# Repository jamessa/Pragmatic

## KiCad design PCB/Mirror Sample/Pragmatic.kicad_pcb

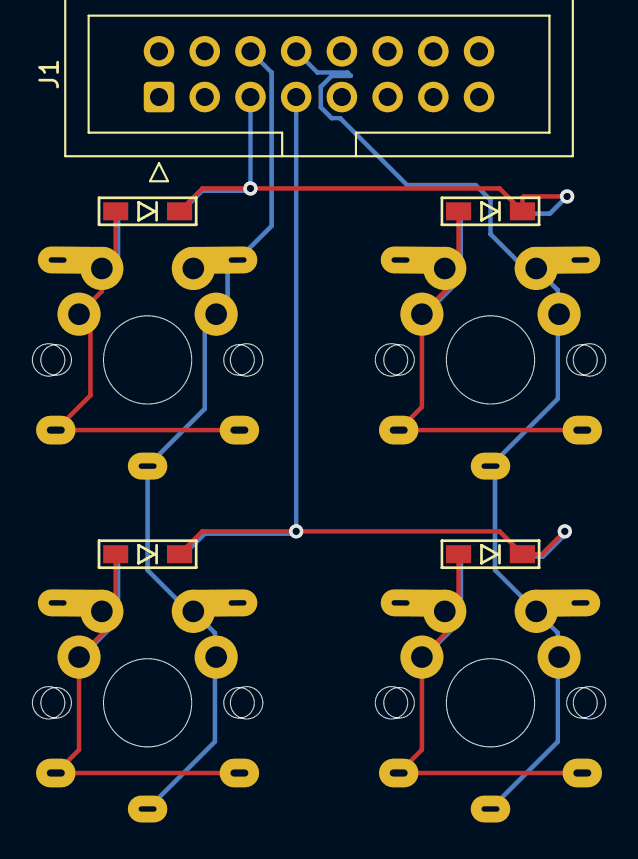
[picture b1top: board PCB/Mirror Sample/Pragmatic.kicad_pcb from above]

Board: 2 copper layers, 9 parts (0 on the bottom side), 8 nets.

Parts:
D1, D2, D7, D8: D; D_SMD
J1: Conn_02x08_Odd_Even; IDC-Header_2x08_P2.54mm_Vertical
SW1, SW2, SW7, SW8: SW_Push; CherryMX_ChocV2_1u

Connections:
Col1: J1.6, SW1.2, SW7.2
Col2: J1.8, SW2.2, SW8.2
unnamed: D1.2, SW1.1
unnamed: D2.2, SW2.1
unnamed: D7.2, SW7.1
unnamed: D8.2, SW8.1
Row1: D1.1, D2.1, J1.5
Row2: D7.1, D8.1, J1.7

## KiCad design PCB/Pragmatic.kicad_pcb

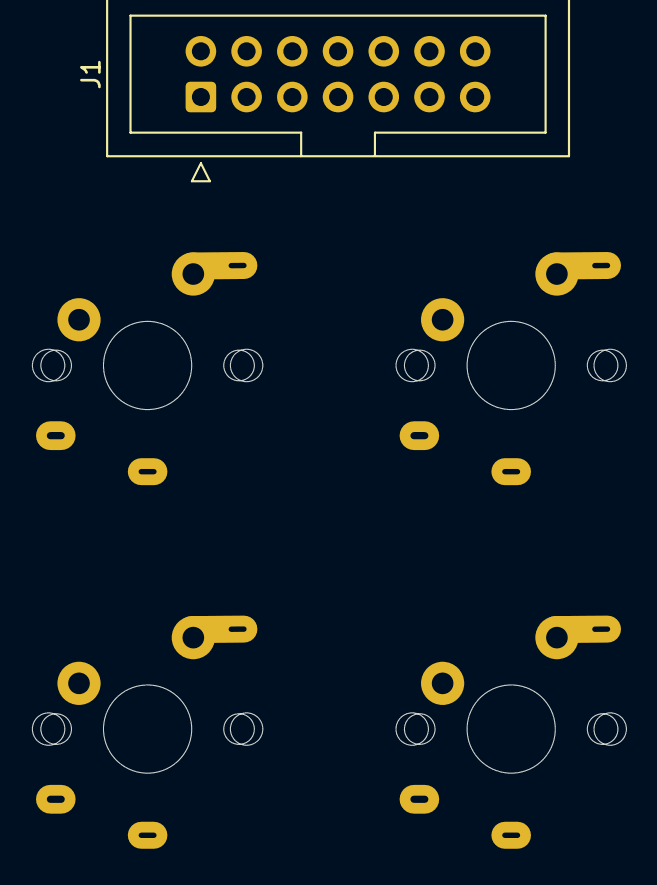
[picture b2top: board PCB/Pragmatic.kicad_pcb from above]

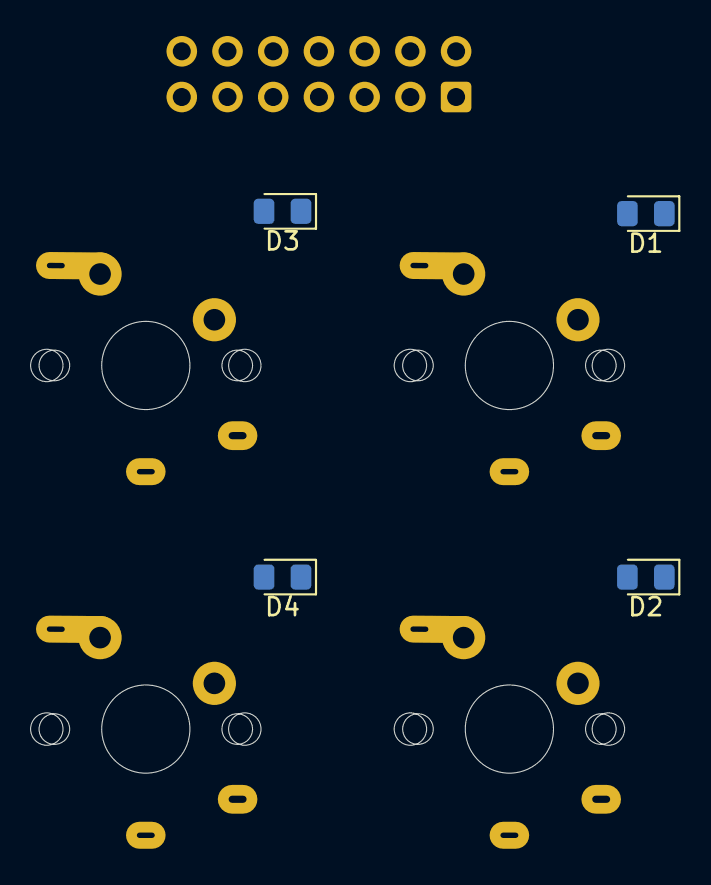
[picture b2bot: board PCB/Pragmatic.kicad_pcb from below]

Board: 2 copper layers, 9 parts (4 on the bottom side), 8 nets, no tracks yet.

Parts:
D1, D2, D3, D4: D; D_0805_2012Metric_Pad1.15x1.40mm_HandSolder
J1: Conn_02x07_Odd_Even; IDC-Header_2x07_P2.54mm_Vertical
SW1, SW2, SW3, SW4: SW_Push; CherryMX_ChocV2_1u

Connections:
Col1: J1.4, SW1.2, SW3.2
Col2: J1.6, SW2.2, SW4.2
unnamed: D1.2, SW1.1
unnamed: D2.2, SW2.1
unnamed: D3.2, SW3.1
unnamed: D4.2, SW4.1
Row1: D1.1, D2.1, J1.3
Row2: D3.1, D4.1, J1.5

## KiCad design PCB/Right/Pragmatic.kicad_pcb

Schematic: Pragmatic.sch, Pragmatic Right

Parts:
D1, D2, D3, D4, D5, D6, D7, D8, D9, D10, D11, D12, D13, D14, D15, D16, D17, D18, D19, D20, D21, D22, D23, D24, D25, D26, D27, D28, D29, D30, D31, D32, D33, D34, D35, D36: D; D3_SMD_v2
D37: LED; LED_D3.0mm
J1: Conn_02x07_Odd_Even; IDC-Header_2x07_P2.54mm_Vertical
R1: 220Ω; R_Axial_DIN0207_L6.3mm_D2.5mm_P10.16mm_Horizontal
SW1, SW2, SW3, SW4, SW5, SW6, SW7, SW8, SW9, SW10, SW11, SW12, SW13, SW14, SW15, SW16, SW17, SW18, SW19, SW20, SW21, SW22, SW23, SW24, SW25, SW26, SW27, SW28, SW29, SW30, SW31, SW32, SW33, SW34, SW35, SW36: SW_Push; CherryMX_ChocV2_1u

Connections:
Col7: J1.9, SW1.2, SW7.2, SW13.2, SW19.2, SW25.2, SW31.2
Col8: J1.10, SW2.2, SW8.2, SW14.2, SW20.2, SW26.2, SW32.2
Col9: J1.11, SW3.2, SW9.2, SW15.2, SW21.2, SW27.2, SW33.2
Col10: J1.12, SW4.2, SW10.2, SW16.2, SW22.2, SW28.2, SW34.2
Col11: J1.13, SW5.2, SW11.2, SW17.2, SW23.2, SW29.2, SW35.2
Col12: J1.14, SW6.2, SW12.2, SW18.2, SW24.2, SW30.2, SW36.2
Ground: D37.1, J1.2
unnamed: D1.2 (A), SW1.1
unnamed: D2.2 (A), SW2.1
unnamed: D3.2 (A), SW3.1
unnamed: D4.2 (A), SW4.1
unnamed: D5.2 (A), SW5.1
unnamed: D6.2 (A), SW6.1
unnamed: D7.2 (A), SW7.1
unnamed: D8.2 (A), SW8.1
unnamed: D9.2 (A), SW9.1
unnamed: D10.2 (A), SW10.1
unnamed: D11.2 (A), SW11.1
unnamed: D12.2 (A), SW12.1
unnamed: D13.2 (A), SW13.1
unnamed: D14.2 (A), SW14.1
unnamed: D15.2 (A), SW15.1
unnamed: D16.2 (A), SW16.1
unnamed: D17.2 (A), SW17.1
unnamed: D18.2 (A), SW18.1
unnamed: D19.2 (A), SW19.1
unnamed: D20.2 (A), SW20.1
unnamed: D21.2 (A), SW21.1
unnamed: D22.2 (A), SW22.1
unnamed: D23.2 (A), SW23.1
unnamed: D24.2 (A), SW24.1
unnamed: D25.2 (A), SW25.1
unnamed: D26.2 (A), SW26.1
unnamed: D27.2 (A), SW27.1
unnamed: D28.2 (A), SW28.1
unnamed: D29.2 (A), SW29.1
unnamed: D30.2 (A), SW30.1
unnamed: D31.2 (A), SW31.1
unnamed: D32.2 (A), SW32.1
unnamed: D33.2 (A), SW33.1
unnamed: D34.2 (A), SW34.1
unnamed: D35.2 (A), SW35.1
unnamed: D36.2 (A), SW36.1
unnamed: D37.2, R1.1
Row1: D1.1 (K), D2.1 (K), D3.1 (K), D4.1 (K), D5.1 (K), D6.1 (K), J1.3
Row2: D7.1 (K), D8.1 (K), D9.1 (K), D10.1 (K), D11.1 (K), D12.1 (K), J1.4
Row3: D13.1 (K), D14.1 (K), D15.1 (K), D16.1 (K), D17.1 (K), D18.1 (K), J1.5
Row4: D19.1 (K), D20.1 (K), D21.1 (K), D22.1 (K), D23.1 (K), D24.1 (K), J1.6
Row5: D25.1 (K), D26.1 (K), D27.1 (K), D28.1 (K), D29.1 (K), D30.1 (K), J1.7
Row6: D31.1 (K), D32.1 (K), D33.1 (K), D34.1 (K), D35.1 (K), D36.1 (K), J1.8
VCC: J1.1, R1.2

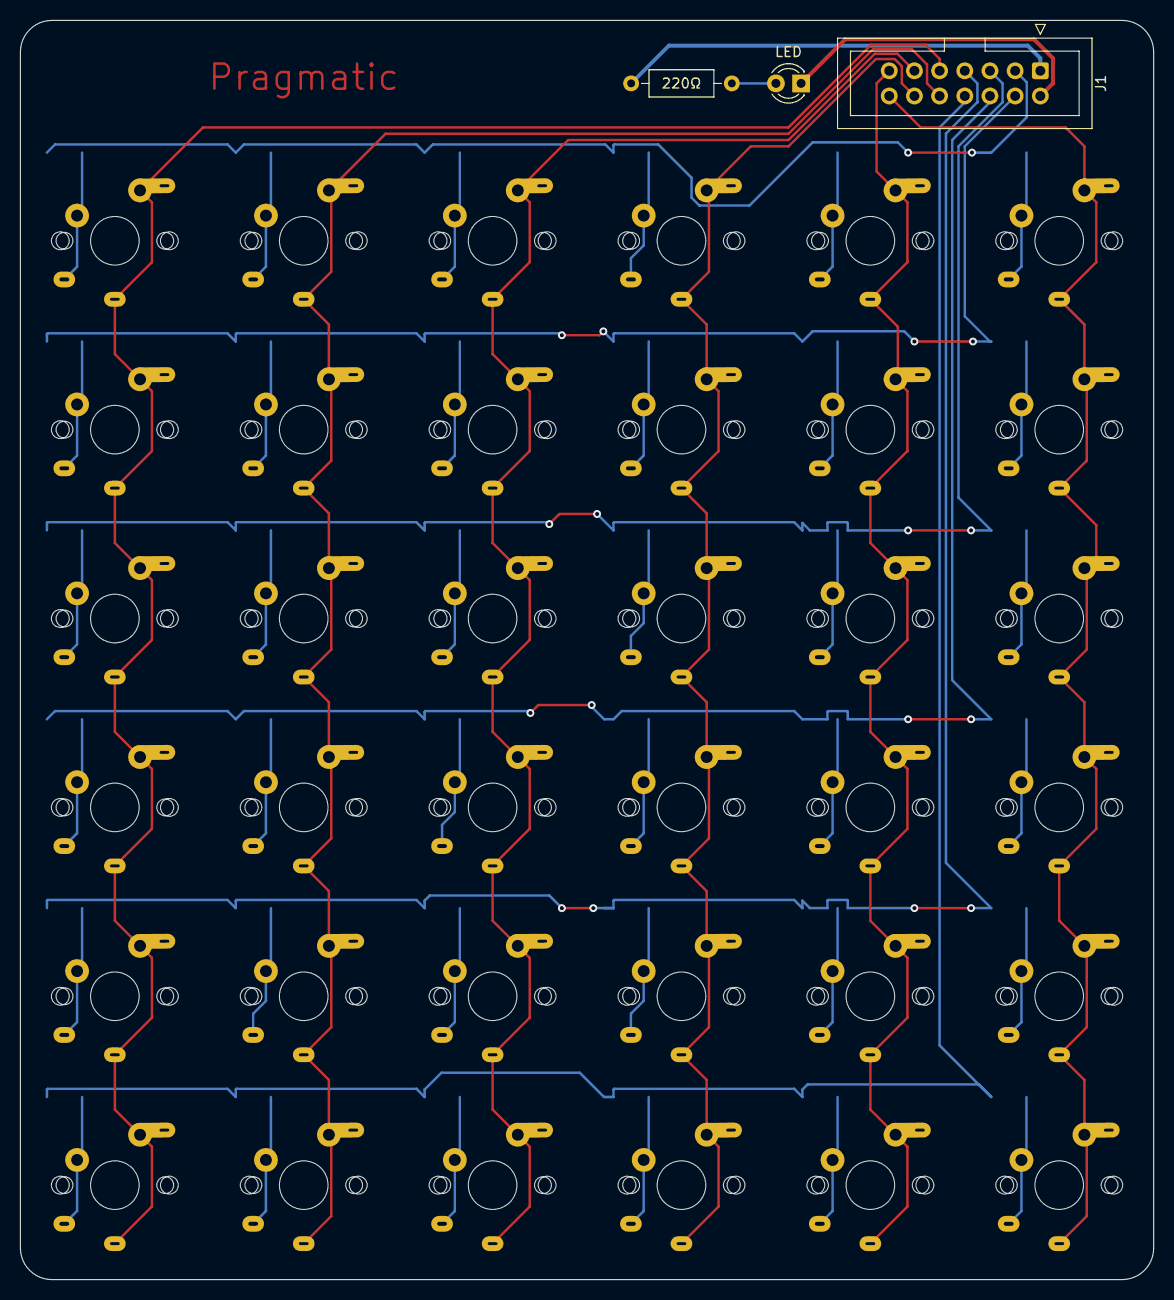
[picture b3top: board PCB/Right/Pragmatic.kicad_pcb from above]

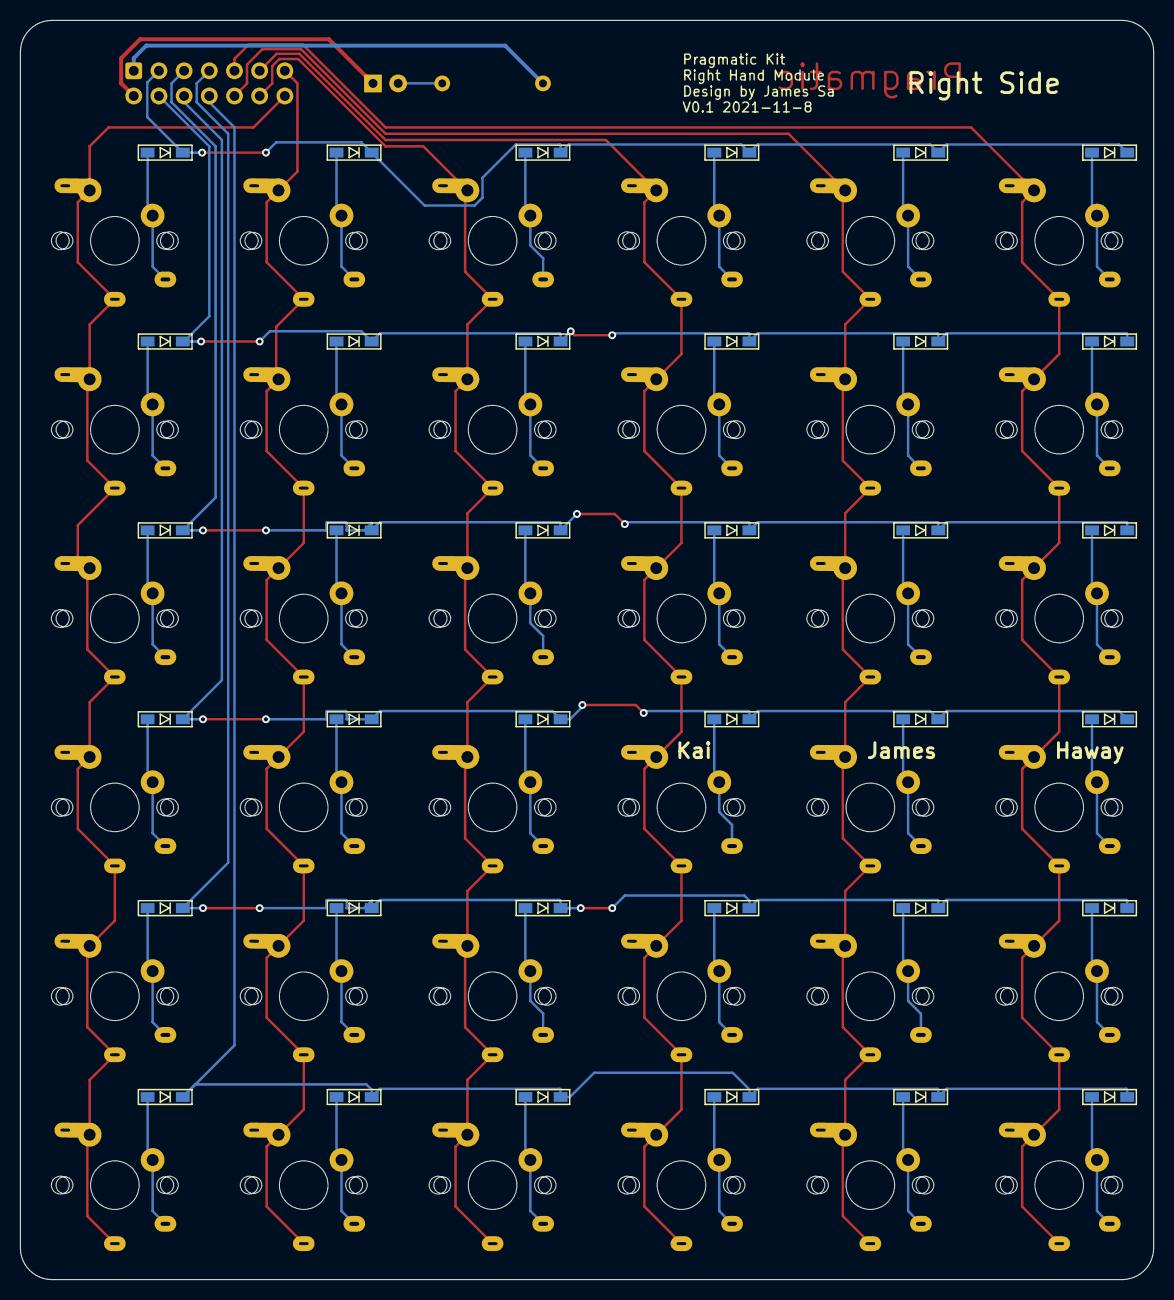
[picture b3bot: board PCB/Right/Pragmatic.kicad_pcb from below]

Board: 2 copper layers, 114.3 x 127.0 mm, 75 parts (36 on the bottom side), 51 nets.

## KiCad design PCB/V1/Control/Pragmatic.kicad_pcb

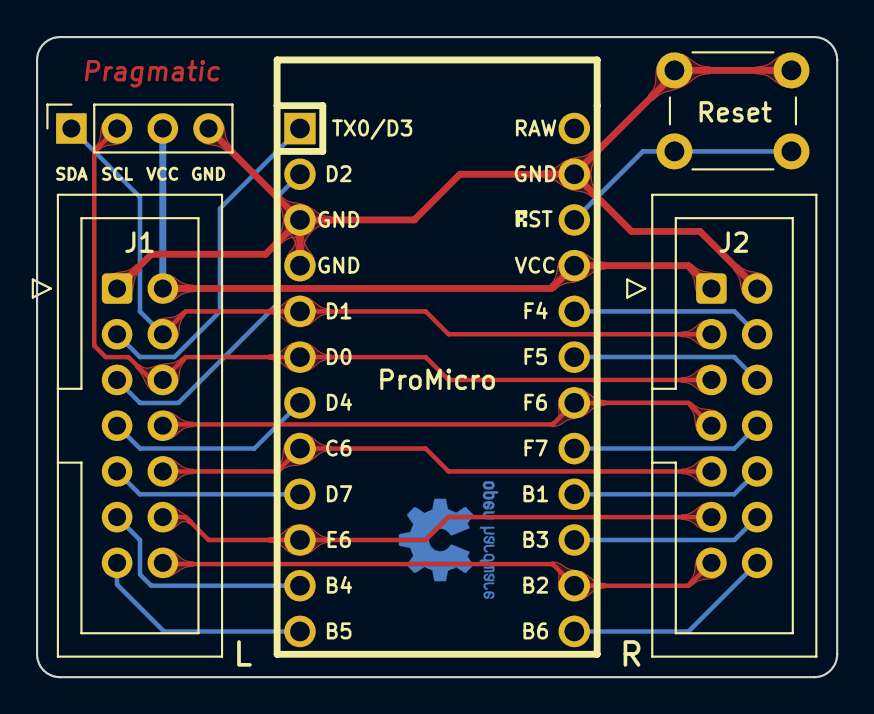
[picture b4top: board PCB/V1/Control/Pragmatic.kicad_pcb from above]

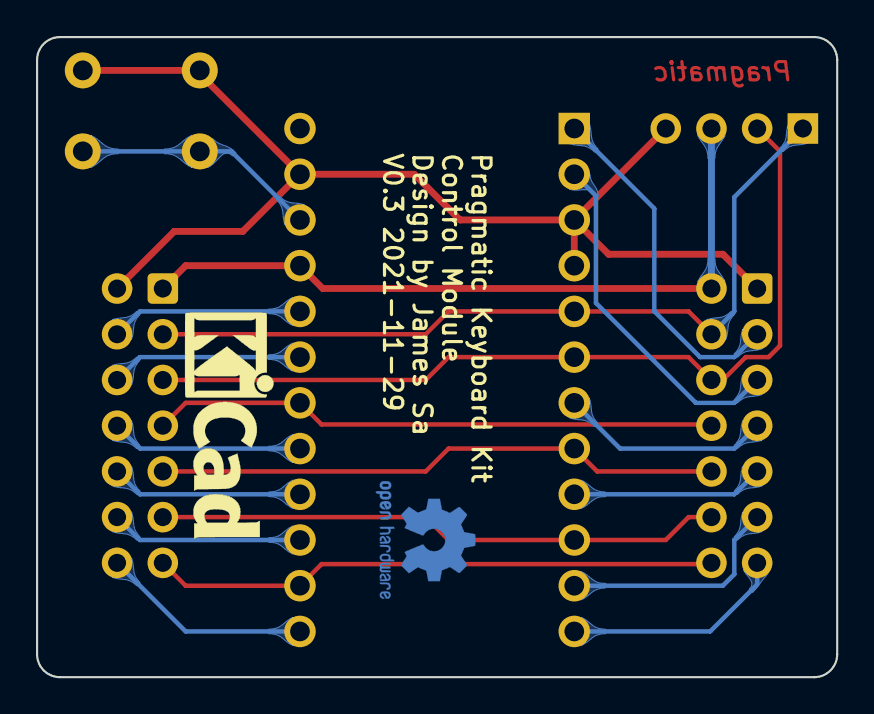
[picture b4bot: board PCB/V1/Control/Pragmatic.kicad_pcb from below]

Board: 2 copper layers, 44.5 x 35.6 mm, 7 parts (2 on the bottom side), 21 nets.

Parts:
J1: L; IDC-Header_2x07_P2.54mm_Vertical
J2: R; IDC-Header_2x07_P2.54mm_Vertical
J3: Conn_01x04; PinSocket_1x04_P2.54mm_Vertical
Logo1: OSHW-Logo2_7.3x6mm_Copper
Logo2: KiCad-Logo_5mm_SilkScreen
SW1: SW_Push; SW_PUSH_6mm
U1: ProMicro; ArduinoProMicro

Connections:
Col1: J1.3, U1.1
Col2: J1.5, U1.2
Col3: J1.7, U1.7
Col4: J1.9, U1.9
Col5: J1.11, U1.11
Col6: J1.13, U1.12
Col7: J2.14, U1.13
Col8: J2.12, U1.15
Col9: J2.10, U1.16
Col10: J2.8, U1.17
Col11: J2.6, U1.19
Col12: J2.4, U1.20
GND: J1.1, J2.2, J3.4, SW1.2, U1.3, U1.4, U1.23
Reset: SW1.1, U1.22
Row1: J1.4, J2.3, J3.1, U1.5
Row2: J1.6, J2.5, J3.2, U1.6
Row3: J1.8, J2.7, U1.18
Row4: J1.10, J2.9, U1.8
Row5: J1.12, J2.11, U1.10
Row6: J1.14, J2.13, U1.14
VCC: J1.2, J2.1, J3.3, U1.21

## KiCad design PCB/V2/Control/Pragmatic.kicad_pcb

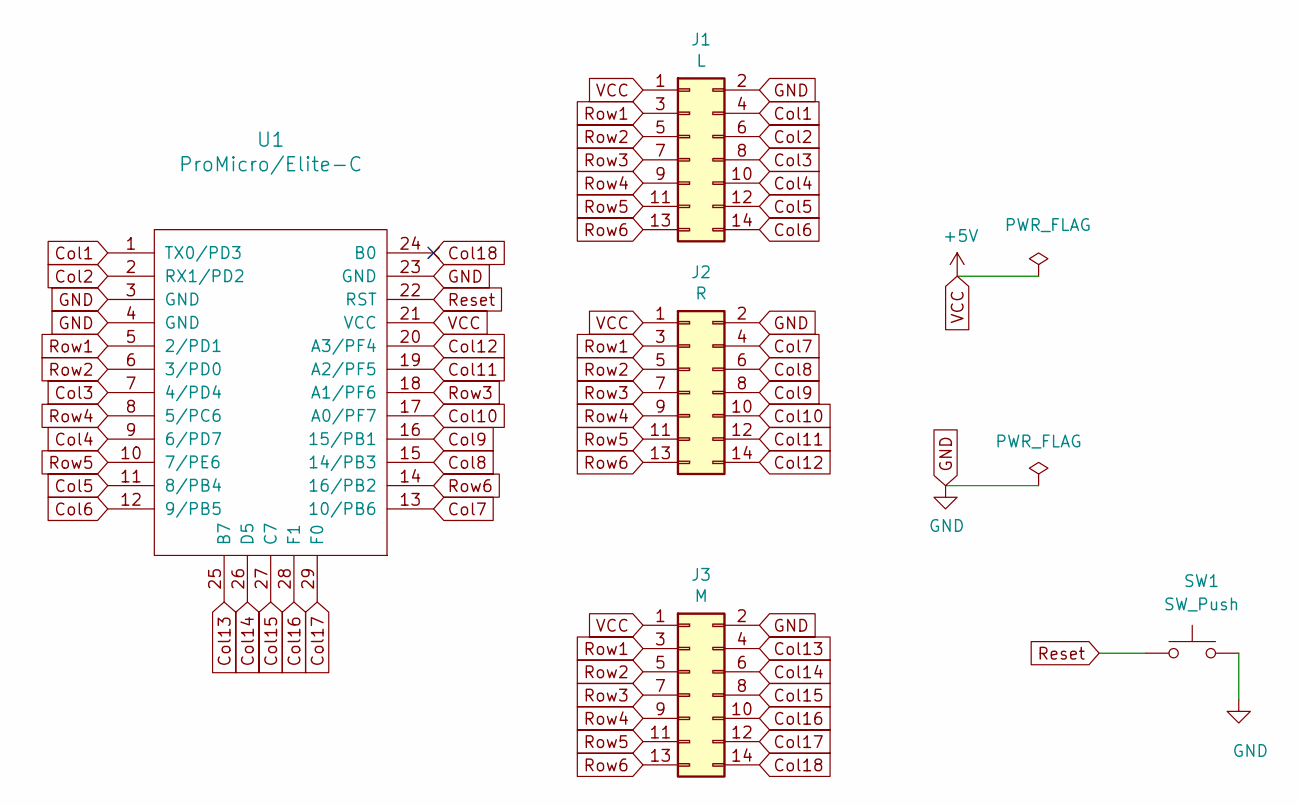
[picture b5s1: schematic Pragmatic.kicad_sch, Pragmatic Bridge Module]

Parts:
J1: L; IDC-Header_2x07_P2.54mm_Vertical; LCSC C3406
J2: R; IDC-Header_2x07_P2.54mm_Vertical; LCSC C3406
J3: M; IDC-Header_2x07_P2.54mm_Vertical; LCSC C3406
SW1: SW_Push; SW_PUSH_6mm; LCSC C620316
U1: ProMicro/Elite-C; Elite-C

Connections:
Col1: J1.4, U1.1 (TX0/PD3)
Col2: J1.6, U1.2 (RX1/PD2)
Col3: J1.8, U1.7 (4/PD4)
Col4: J1.10, U1.9 (6/PD7)
Col5: J1.12, U1.11 (8/PB4)
Col6: J1.14, U1.12 (9/PB5)
Col7: J2.4, U1.13 (10/PB6)
Col8: J2.6, U1.15 (14/PB3)
Col9: J2.8, U1.16 (15/PB1)
Col10: J2.10, U1.17 (A0/PF7)
Col11: J2.12, U1.19 (A2/PF5)
Col12: J2.14, U1.20 (A3/PF4)
Col13: J3.4, U1.25 (B7)
Col14: J3.6, U1.26 (D5)
Col15: J3.8, U1.27 (C7)
Col16: J3.10, U1.28 (F1)
Col17: J3.12, U1.29 (F0)
Col18: J3.14, U1.24 (B0)
GND: J1.2, J2.2, J3.2, SW1.2, U1.3 (GND), U1.4 (GND), U1.23 (GND)
Reset: SW1.1, U1.22 (RST)
Row1: J1.3, J2.3, J3.3, U1.5 (2/PD1)
Row2: J1.5, J2.5, J3.5, U1.6 (3/PD0)
Row3: J1.7, J2.7, J3.7, U1.18 (A1/PF6)
Row4: J1.9, J2.9, J3.9, U1.8 (5/PC6)
Row5: J1.11, J2.11, J3.11, U1.10 (7/PE6)
Row6: J1.13, J2.13, J3.13, U1.14 (16/PB2)
VCC: J1.1, J2.1, J3.1, U1.21 (VCC)

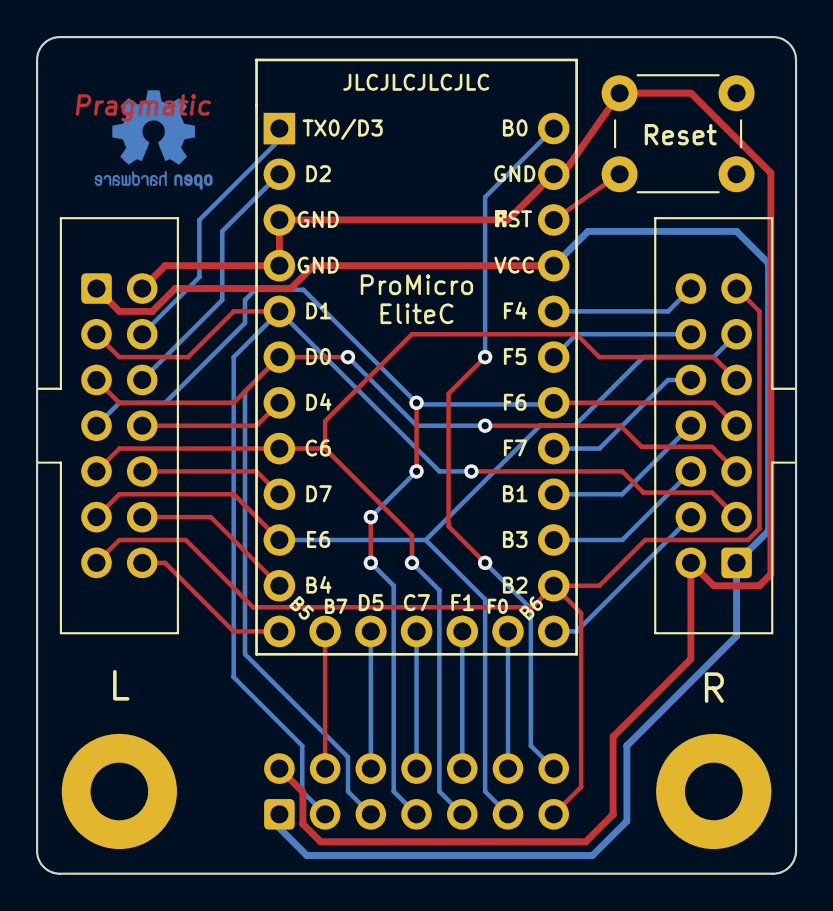
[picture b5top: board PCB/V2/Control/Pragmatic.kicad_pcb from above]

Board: 2 copper layers, 42.2 x 46.5 mm, 9 parts (1 on the bottom side), 27 nets.

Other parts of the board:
L1: JLC Legend
Logo1: OSHW-Logo2_7.3x6mm_Copper
M1, M2: MountingHole_3.2mm_M3_Pad
